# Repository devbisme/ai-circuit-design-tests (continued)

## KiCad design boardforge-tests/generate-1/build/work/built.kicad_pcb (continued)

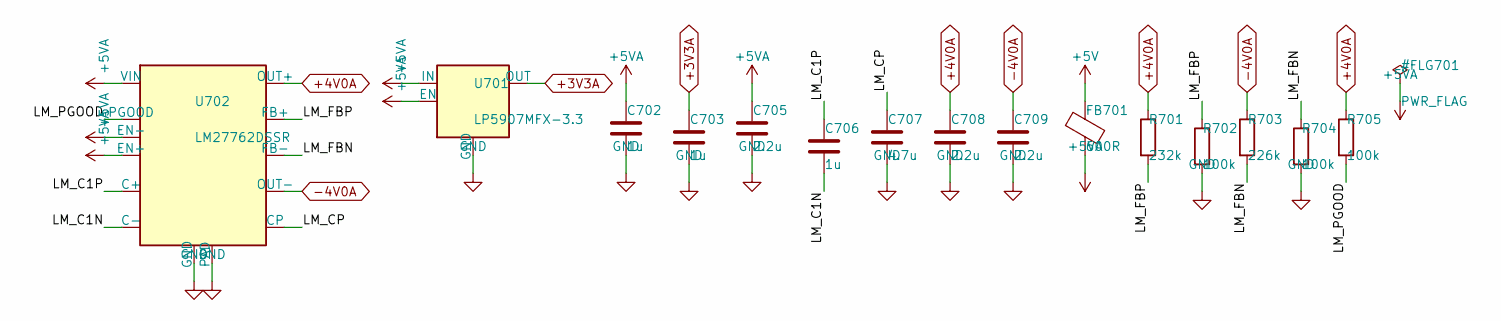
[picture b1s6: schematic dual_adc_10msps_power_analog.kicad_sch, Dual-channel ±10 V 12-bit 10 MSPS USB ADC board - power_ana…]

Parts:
C702, C703, C706: 1u; C_0402_1005Metric; MPN CL05A105KA5NQNC; LCSC C52923
C705, C708, C709: 2.2u; C_0603_1608Metric; MPN CL10A225KO8NNNC; LCSC C23630
C707: 4.7u; C_0603_1608Metric; MPN CL10A475KO8NNNC; LCSC C19666
FB701: 600R; L_0603_1608Metric; MPN BLM18KG601SN1D; LCSC C85833
R701: 232k; R_0402_1005Metric; MPN FRC0402F2323TS; LCSC C3013159
R702, R704, R705: 100k; R_0402_1005Metric; MPN 0402WGF1003TCE; LCSC C25741
R703: 226k; R_0402_1005Metric; MPN FRC0402F2263TS; LCSC C5121518
U701: LP5907MFX-3.3; SOT-23-5; MPN LP5907MFX-3.3/NOPB; LCSC C80670
U702: LM27762DSSR; WSON-12-1EP_3x2mm_P0.5mm_EP1x2.65; MPN LM27762DSSR; LCSC C473398

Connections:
+3V3A: C703.1, U701.5 (OUT); also elsewhere on the board
+4V0A: C708.1, R701.1, R705.1, U702.11 (OUT+); also elsewhere on the board
+5V: FB701.1; also elsewhere on the board
+5VA: C702.1, C705.1, FB701.2, U701.1 (IN), U701.3 (EN), U702.3 (VIN), U702.8 (EN-), U702.12 (EN+)
-4V0A: C709.1, R703.1, U702.6 (OUT-); also elsewhere on the board
/power_analog/LM_C1N: C706.2, U702.9 (C-)
/power_analog/LM_C1P: C706.1, U702.10 (C+)
/power_analog/LM_CP: C707.1, U702.5 (CP)
/power_analog/LM_FBN: R703.2, R704.1, U702.7 (FB-)
/power_analog/LM_FBP: R701.2, R702.1, U702.2 (FB+)
/power_analog/LM_PGOOD: R705.2, U702.1 (PGOOD)
GND: C702.2, C703.2, C705.2, C707.2, C708.2, C709.2, R702.2, R704.2, U701.2 (GND), U702.4 (GND), U702.13 (PAD); also elsewhere on the board

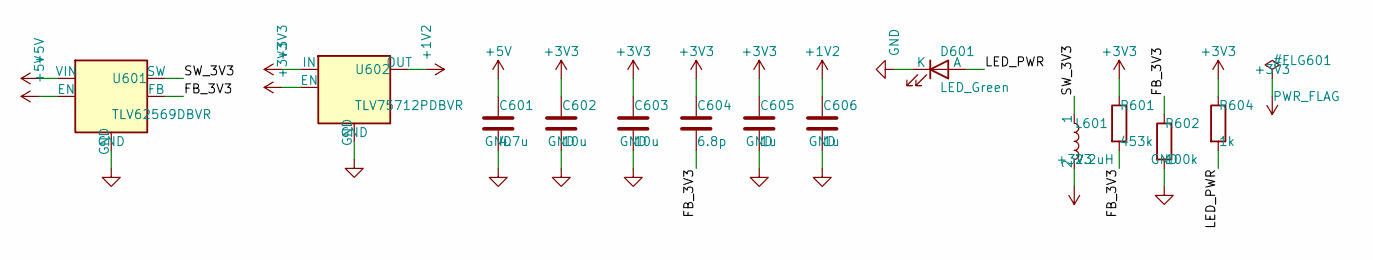
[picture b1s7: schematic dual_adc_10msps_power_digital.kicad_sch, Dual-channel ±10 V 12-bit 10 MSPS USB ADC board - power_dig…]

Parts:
C601: 4.7u; C_0603_1608Metric; MPN CL10A475KO8NNNC; LCSC C19666
C602, C603: 10u; C_0603_1608Metric; MPN CL10A106KP8NNNC; LCSC C19702
C604: 6.8p; C_0402_1005Metric; MPN 0402CG6R8C500NT; LCSC C1576
C605, C606: 1u; C_0402_1005Metric; MPN CL05A105KA5NQNC; LCSC C52923
D601: LED_Green; LED_0603_1608Metric; MPN PSC-1608U52GC-G4; LCSC C22371297
L601: 2.2uH; L_1008_2520Metric; MPN TMS252012ALM-2R2MTAA; LCSC C1017131
R601: 453k; R_0402_1005Metric; MPN 0402WGF4533TCE; LCSC C27009
R602: 100k; R_0402_1005Metric; MPN 0402WGF1003TCE; LCSC C25741
R604: 1k; R_0402_1005Metric; MPN 0402WGF1001TCE; LCSC C11702
U601: TLV62569DBVR; SOT-23-5; MPN TLV62569DBVR; LCSC C141836
U602: TLV75712PDBVR; SOT-23-5; MPN TLV75712PDBVR; LCSC C1509296

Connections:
+1V2: C606.1, U602.5 (OUT); also elsewhere on the board
+3V3: C602.1, C603.1, C604.1, C605.1, L601.2, R601.1, R604.1, U602.1 (IN), U602.3 (EN); also elsewhere on the board
+5V: C601.1, U601.1 (EN), U601.4 (VIN); also elsewhere on the board
/power_digital/FB_3V3: C604.2, R601.2, R602.1, U601.5 (FB)
/power_digital/LED_PWR: D601.2 (A), R604.2
/power_digital/SW_3V3: L601.1, U601.3 (SW)
GND: C601.2, C602.2, C603.2, C605.2, C606.2, D601.1 (K), R602.2, U601.2 (GND), U602.2 (GND); also elsewhere on the board

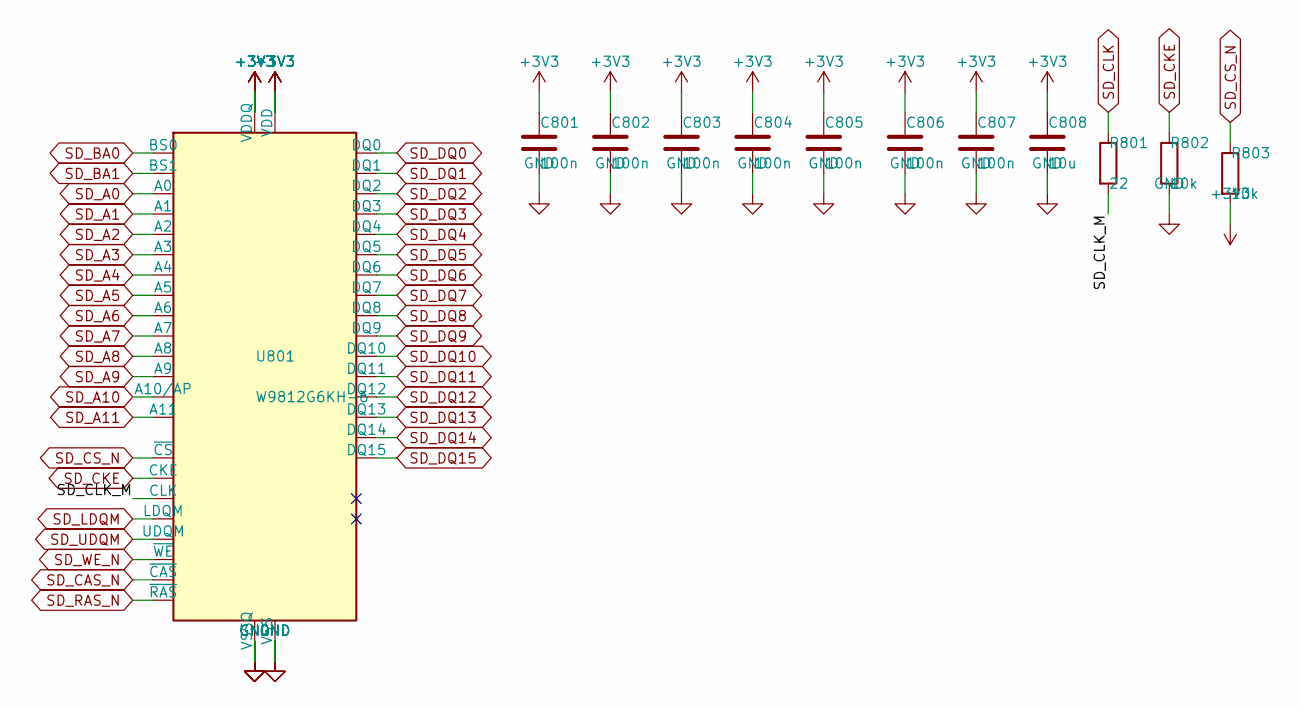
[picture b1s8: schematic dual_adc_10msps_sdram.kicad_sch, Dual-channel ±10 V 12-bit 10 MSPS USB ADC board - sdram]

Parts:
C801, C802, C803, C804, C805, C806, C807: 100n; C_0402_1005Metric; MPN CL05B104KB54PNC; LCSC C307331
C808: 10u; C_0603_1608Metric; MPN CL10A106KP8NNNC; LCSC C19702
R801: 22; R_0402_1005Metric; MPN 0402WGF220JTCE; LCSC C25092
R802, R803: 10k; R_0402_1005Metric; MPN 0402WGF1002TCE; LCSC C25744
U801: W9812G6KH-6; TSOP-II-54_22.2x10.16mm_P0.8mm; MPN W9812G6KH-6; LCSC C62379

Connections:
+3V3: C801.1, C802.1, C803.1, C804.1, C805.1, C806.1, C807.1, C808.1, R803.2, U801.1 (VDD), U801.3 (VDDQ), U801.9 (VDDQ), U801.14 (VDD), U801.27 (VDD), U801.43 (VDDQ), U801.49 (VDDQ); also elsewhere on the board
/sdram/SD_CLK_M: R801.2, U801.38 (CLK)
GND: C801.2, C802.2, C803.2, C804.2, C805.2, C806.2, C807.2, C808.2, R802.2, U801.6 (VSSQ), U801.12 (VSSQ), U801.28 (VSS), U801.41 (VSS), U801.46 (VSSQ), U801.52 (VSSQ), U801.54 (VSS); also elsewhere on the board
SD_A0: U801.23 (A0); also elsewhere on the board
SD_A1: U801.24 (A1); also elsewhere on the board
SD_A2: U801.25 (A2); also elsewhere on the board
SD_A3: U801.26 (A3); also elsewhere on the board
SD_A4: U801.29 (A4); also elsewhere on the board
SD_A5: U801.30 (A5); also elsewhere on the board
SD_A6: U801.31 (A6); also elsewhere on the board
SD_A7: U801.32 (A7); also elsewhere on the board
SD_A8: U801.33 (A8); also elsewhere on the board
SD_A9: U801.34 (A9); also elsewhere on the board
SD_A10: U801.22 (A10/AP); also elsewhere on the board
SD_A11: U801.35 (A11); also elsewhere on the board
SD_BA0: U801.20 (BS0); also elsewhere on the board
SD_BA1: U801.21 (BS1); also elsewhere on the board
SD_CAS_N: U801.17 (~CAS); also elsewhere on the board
SD_CKE: R802.1, U801.37 (CKE); also elsewhere on the board
SD_CLK: R801.1; also elsewhere on the board
SD_CS_N: R803.1, U801.19 (~CS); also elsewhere on the board
SD_DQ0: U801.2 (DQ0); also elsewhere on the board
SD_DQ1: U801.4 (DQ1); also elsewhere on the board
SD_DQ2: U801.5 (DQ2); also elsewhere on the board
SD_DQ3: U801.7 (DQ3); also elsewhere on the board
SD_DQ4: U801.8 (DQ4); also elsewhere on the board
SD_DQ5: U801.10 (DQ5); also elsewhere on the board
SD_DQ6: U801.11 (DQ6); also elsewhere on the board
SD_DQ7: U801.13 (DQ7); also elsewhere on the board
SD_DQ8: U801.42 (DQ8); also elsewhere on the board
SD_DQ9: U801.44 (DQ9); also elsewhere on the board
SD_DQ10: U801.45 (DQ10); also elsewhere on the board
SD_DQ11: U801.47 (DQ11); also elsewhere on the board
SD_DQ12: U801.48 (DQ12); also elsewhere on the board
SD_DQ13: U801.50 (DQ13); also elsewhere on the board
SD_DQ14: U801.51 (DQ14); also elsewhere on the board
SD_DQ15: U801.53 (DQ15); also elsewhere on the board
SD_LDQM: U801.15 (LDQM); also elsewhere on the board
SD_RAS_N: U801.18 (~RAS); also elsewhere on the board
SD_UDQM: U801.39 (UDQM); also elsewhere on the board
SD_WE_N: U801.16 (~WE); also elsewhere on the board

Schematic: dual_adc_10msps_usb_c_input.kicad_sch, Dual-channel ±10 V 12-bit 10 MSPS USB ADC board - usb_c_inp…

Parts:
C501: 1u; C_0402_1005Metric; MPN CL05A105KA5NQNC; LCSC C52923
D501: SMF5.0A; D_SOD-123F; MPN SMF5.0A; LCSC C19077497
F501: 750mA; Fuse_1812_4532Metric; MPN JK-mSMD075-33; LCSC C369169
J501: TYPE-C-31-M-12; USB_C_Receptacle_HRO_TYPE-C-31-M-12; MPN TYPE-C-31-M-12; LCSC C165948
R501, R502: 5.1k; R_0402_1005Metric; MPN 0402WGF5101TCE; LCSC C25905
U501: USBLC6-2SC6; SOT-23-6; MPN USBLC6-2SC6; LCSC C7519

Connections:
+5V: F501.2; also elsewhere on the board
/usb_c_input/CC1: J501.A5 (CC1), R501.1
/usb_c_input/CC2: J501.B5 (CC2), R502.1
GND: C501.2, D501.2 (A2), J501.A1 (GND), J501.A12 (GND), J501.B1 (GND), J501.B12 (GND), J501.SH (SHIELD), R501.2, R502.2, U501.2 (GND); also elsewhere on the board
USB_DM: J501.A7 (D-), J501.B7 (D-), U501.3 (I/O2), U501.4 (I/O2); also elsewhere on the board
USB_DP: J501.A6 (D+), J501.B6 (D+), U501.1 (I/O1), U501.6 (I/O1); also elsewhere on the board
VBUS: C501.1, D501.1 (A1), F501.1, J501.A4 (VBUS), J501.A9 (VBUS), J501.B4 (VBUS), J501.B9 (VBUS), U501.5 (VBUS)

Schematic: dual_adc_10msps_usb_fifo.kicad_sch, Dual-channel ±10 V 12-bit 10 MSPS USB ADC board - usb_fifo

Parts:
C901, C902: 18p; C_0402_1005Metric; MPN 0402CG180J500NT; LCSC C1549
C903, C909: 4.7u; C_0603_1608Metric; MPN CL10A475KO8NNNC; LCSC C19666
C904, C905, C906, C907, C908, C910, C911, C912, C913: 100n; C_0402_1005Metric; MPN CL05B104KB54PNC; LCSC C307331
FB901: 600R; L_0603_1608Metric; MPN BLM18KG601SN1D; LCSC C85833
R901: 12k; R_0402_1005Metric; MPN 0402WGF1202TCE; LCSC C25752
R902, R904, R905, R906, R907, R908, R909, R911, R912: 10k; R_0402_1005Metric; MPN 0402WGF1002TCE; LCSC C25744
R903: 2.2k; R_0402_1005Metric; MPN 0402WGF2201TCE; LCSC C25879
R910: 22; R_0402_1005Metric; MPN 0402WGF220JTCE; LCSC C25092
U901: FT232HL; LQFP-48_7x7mm_P0.5mm; MPN FT232HL; LCSC C51997
U902: 93LC56BT-I/OT; SOT-23-6; MPN 93LC56BT-I/OT; LCSC C190271
Y901: 12MHz; Crystal_SMD_2520-4Pin_2.5x2.0mm; MPN TXM12M0004252FBCEO00T; LCSC C284155

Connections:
+3V3: C906.1, C907.1, C908.1, C909.1, C910.1, C913.1, FB901.1, R902.2, R904.2, R905.2, R906.2, R907.2, R908.2, R909.2, R911.2, R912.2, U901.12 (VCCIO), U901.24 (VCCIO), U901.39 (VCCD), U901.40 (VREGIN), U901.46 (VCCIO), U902.6 (VCC); also elsewhere on the board
/usb_fifo/+3V3_PHY: C903.1, C904.1, C905.1, FB901.2, U901.3 (VPHY), U901.8 (VPLL)
/usb_fifo/EE_CLK: R905.1, U901.44 (EECLK), U902.4 (CLK)
/usb_fifo/EE_CS: R904.1, U901.45 (EECS), U902.5 (CS)
/usb_fifo/EE_DATA: R903.2, R906.1, U901.43 (EEDATA), U902.3 (DI)
/usb_fifo/EE_DO: R903.1, U902.1 (DO)
/usb_fifo/FT_CLKOUT_S: R910.1, U901.29 (ACBUS5)
/usb_fifo/FT_PWRSAV_N: R912.1, U901.31 (ACBUS7)
/usb_fifo/FT_REF: R901.1, U901.5 (REF)
/usb_fifo/FT_RESET_N: R902.1, U901.34 (~RESET)
/usb_fifo/FT_SIWU_N: R909.1, U901.28 (ACBUS4)
/usb_fifo/FT_VCCA: C912.1, U901.37 (VCCA)
/usb_fifo/FT_VCORE: C911.1, U901.38 (VCCCORE)
/usb_fifo/FT_XI: C901.1, U901.1 (XCSI), Y901.1
/usb_fifo/FT_XO: C902.1, U901.2 (XCSO), Y901.3
FT_CLKOUT: R910.2; also elsewhere on the board
FT_D0: U901.13 (ADBUS0); also elsewhere on the board
FT_D1: U901.14 (ADBUS1); also elsewhere on the board
FT_D2: U901.15 (ADBUS2); also elsewhere on the board
FT_D3: U901.16 (ADBUS3); also elsewhere on the board
FT_D4: U901.17 (ADBUS4); also elsewhere on the board
FT_D5: U901.18 (ADBUS5); also elsewhere on the board
FT_D6: U901.19 (ADBUS6); also elsewhere on the board
FT_D7: U901.20 (ADBUS7); also elsewhere on the board
FT_OE_N: R911.1, U901.30 (ACBUS6); also elsewhere on the board
FT_RD_N: R907.1, U901.26 (ACBUS2); also elsewhere on the board
FT_RXF_N: U901.21 (ACBUS0); also elsewhere on the board
FT_TXE_N: U901.25 (ACBUS1); also elsewhere on the board
FT_WR_N: R908.1, U901.27 (ACBUS3); also elsewhere on the board
GND: C901.2, C902.2, C903.2, C904.2, C905.2, C906.2, C907.2, C908.2, C909.2, C910.2, C911.2, C912.2, C913.2, R901.2, U901.4 (AGND), U901.9 (AGND), U901.10 (GND), U901.11 (GND), U901.22 (GND), U901.23 (GND), U901.35 (GND), U901.36 (GND), U901.41 (AGND), U901.42 (TEST), U901.47 (GND), U901.48 (GND), U902.2 (GND), Y901.2 (G), Y901.4 (G); also elsewhere on the board
USB_DM: U901.6 (DM); also elsewhere on the board
USB_DP: U901.7 (DP); also elsewhere on the board

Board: 4 copper layers, 243 parts (0 on the bottom side), 217 nets, no tracks yet.

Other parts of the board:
H1, H2, H3, H4: MountingHole; MountingHole_3.2mm_M3_Pad_Via

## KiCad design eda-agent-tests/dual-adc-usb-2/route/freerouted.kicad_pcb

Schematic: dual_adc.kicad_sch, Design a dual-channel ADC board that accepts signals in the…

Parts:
C1, C11, C18, C25: 4.7uF
C2, C4, C6, C7, C10, C49, C50, C54, C55: 1uF
C3, C5, C8, C61, C69, C80, C81, C83, C93: 10uF
C9, C12, C13, C48, C51, C53, C56: 2.2uF
C14: 4.7nF
C15, C19, C20, C21, C22, C23, C24, C26, C27, C28, C29, C30, C36, C37, C44, C45, C47, C52, C57, C58, C59, C60, C62, C63, C64, C65, C66, C67, C68, C70, C71, C72, C73, C74, C75, C76, C77, C78, C79, C82, C84, C85, C86, C87, C88, C89, C90, C91, C92: 100nF
C16, C17: 27pF
C31, C39: 12pF
C32, C40: 2.7pF
C33, C41: 22pF
C34, C35, C42, C43: 33pF
C38, C46: 100pF
D1: Green
D2, D3: BAV99
D4, D5: Yellow
F1: 750mA
FB1: 120R@100MHz 2A
FB2, FB3: 600R@100MHz
H1, H2, H3, H4: MountingHole
J1: USB_B
J2: BNC_A
J3: BNC_B
J4: PROG
R1, R9, R10, R12, R13, R14, R33, R40, R41, R42, R43, R44: 10k
R2: 232k
R3, R5: 100k
R4: 226k
R6, R17, R18, R19, R20, R21, R26, R27, R28, R29, R30, R45, R46: 1k
R7: 1M
R8: 12k
R11: 2.2k
R15, R24: 909k
R16, R25: 90.9k
R22, R23, R31, R32: 49.9
R34: 20k
R35, R36, R37: 33
R38, R39: 100
RN1, RN2, RN3, RN4, RN5, RN6, RN7: 33
U1: AP2112K-3.3
U2: AP2112K-1.2
U3: LP5907MFX-3.3
U4: LM27762
U5: USBLC6-2SC6
U6: FT232HL
U7: 93LC56B
U8: OPA1656ID
U9, U10: THS4521ID
U11: LTC2290CUP
U12: ICE40HX4K-TQ144
U13: W25Q32JVSS
U14: MT48LC16M16A2TG-6A
X1: ASE-10.000MHz
Y1: 12MHz

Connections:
+1V2: C5.1, C65.1, C66.1, C67.1, C68.1, C69.1, R38.1, R39.1; also elsewhere on the board
+3V3A: C7.1, C8.1, C36.1, C44.1, C57.1, C58.1, C59.1, C60.1, C61.1, FB3.1, R33.1; also elsewhere on the board
+4V: C12.1, C29.1, D2.2 (A), D3.2 (A), R2.1, U4.11 (OUT+); also elsewhere on the board
+5V: C1.1, C2.1, C6.1, C9.1, FB1.2, U4.3 (VIN), U4.8 (EN-), U4.12 (EN+); also elsewhere on the board
-4V: C13.1, C30.1, D2.1 (K), D3.1 (K), R4.1, U4.6 (OUT-); also elsewhere on the board
ADC_CLKA: R35.2; also elsewhere on the board
ADC_CLKB: R36.2; also elsewhere on the board
ADC_DA0: RN1.8 (R1.2); also elsewhere on the board
ADC_DA0_R: RN1.1 (R1.1); also elsewhere on the board
ADC_DA1: RN1.7 (R2.2); also elsewhere on the board
ADC_DA1_R: RN1.2 (R2.1); also elsewhere on the board
ADC_DA2: RN1.6 (R3.2); also elsewhere on the board
ADC_DA2_R: RN1.3 (R3.1); also elsewhere on the board
ADC_DA3: RN1.5 (R4.2); also elsewhere on the board
ADC_DA3_R: RN1.4 (R4.1); also elsewhere on the board
ADC_DA4: RN2.8 (R1.2); also elsewhere on the board
ADC_DA4_R: RN2.1 (R1.1); also elsewhere on the board
ADC_DA5: RN2.7 (R2.2); also elsewhere on the board
ADC_DA5_R: RN2.2 (R2.1); also elsewhere on the board
ADC_DA6: RN2.6 (R3.2); also elsewhere on the board
ADC_DA6_R: RN2.3 (R3.1); also elsewhere on the board
ADC_DA7: RN2.5 (R4.2); also elsewhere on the board
ADC_DA7_R: RN2.4 (R4.1); also elsewhere on the board
ADC_DA8: RN3.8 (R1.2); also elsewhere on the board
ADC_DA8_R: RN3.1 (R1.1); also elsewhere on the board
ADC_DA9: RN3.7 (R2.2); also elsewhere on the board
ADC_DA9_R: RN3.2 (R2.1); also elsewhere on the board
ADC_DA10: RN3.6 (R3.2); also elsewhere on the board
ADC_DA10_R: RN3.3 (R3.1); also elsewhere on the board
ADC_DA11: RN3.5 (R4.2); also elsewhere on the board
ADC_DA11_R: RN3.4 (R4.1); also elsewhere on the board
ADC_DB0: RN4.7 (R2.2); also elsewhere on the board
ADC_DB0_R: RN4.2 (R2.1); also elsewhere on the board
ADC_DB1: RN4.6 (R3.2); also elsewhere on the board
ADC_DB1_R: RN4.3 (R3.1); also elsewhere on the board
ADC_DB2: RN4.5 (R4.2); also elsewhere on the board
ADC_DB2_R: RN4.4 (R4.1); also elsewhere on the board
ADC_DB3: RN5.8 (R1.2); also elsewhere on the board
ADC_DB3_R: RN5.1 (R1.1); also elsewhere on the board
ADC_DB4: RN5.7 (R2.2); also elsewhere on the board
ADC_DB4_R: RN5.2 (R2.1); also elsewhere on the board
ADC_DB5: RN5.6 (R3.2); also elsewhere on the board
ADC_DB5_R: RN5.3 (R3.1); also elsewhere on the board
ADC_DB6: RN5.5 (R4.2); also elsewhere on the board
ADC_DB6_R: RN5.4 (R4.1); also elsewhere on the board
ADC_DB7: RN6.8 (R1.2); also elsewhere on the board
ADC_DB7_R: RN6.1 (R1.1); also elsewhere on the board
ADC_DB8: RN6.7 (R2.2); also elsewhere on the board
ADC_DB8_R: RN6.2 (R2.1); also elsewhere on the board
ADC_DB9: RN6.6 (R3.2); also elsewhere on the board
ADC_DB9_R: RN6.3 (R3.1); also elsewhere on the board
ADC_DB10: RN6.5 (R4.2); also elsewhere on the board
ADC_DB10_R: RN6.4 (R4.1); also elsewhere on the board
ADC_DB11: RN7.8 (R1.2); also elsewhere on the board
ADC_DB11_R: RN7.1 (R1.1); also elsewhere on the board
ADC_MODE: R33.2, R34.1; also elsewhere on the board
ADC_OFA: RN4.8 (R1.2); also elsewhere on the board
ADC_OFA_R: RN4.1 (R1.1); also elsewhere on the board
ADC_OFB: RN7.7 (R2.2); also elsewhere on the board
ADC_OFB_R: RN7.2 (R2.1); also elsewhere on the board
AINA_N: C38.2, R23.2; also elsewhere on the board
AINA_P: C38.1, R22.2; also elsewhere on the board
AINB_N: C46.2, R32.2; also elsewhere on the board
AINB_P: C46.1, R31.2; also elsewhere on the board
CDONE: J4.8, R40.2; also elsewhere on the board
CFG_SCK: J4.3, U13.6 (CLK); also elsewhere on the board
CFG_SI: J4.7, U13.2 (DO/IO_{1}); also elsewhere on the board
CFG_SO: J4.5, U13.5 (DI/IO_{0}); also elsewhere on the board
CFG_SS_N: J4.1, R42.2, U13.1 (~CS); also elsewhere on the board
CLK10: R35.1, R36.1, R37.1, X1.3 (OUT)
CRESET_N: J4.4, R41.2; also elsewhere on the board
FDAA_ON: C34.1, R19.1, R23.1; also elsewhere on the board
FDAA_OP: C35.1, R21.1, R22.1; also elsewhere on the board
FDAA_SN: C35.2, R20.2, R21.2; also elsewhere on the board
FDAA_SP: C34.2, R18.2, R19.2; also elsewhere on the board
FDAB_ON: C42.1, R28.1, R32.1; also elsewhere on the board
FDAB_OP: C43.1, R30.1, R31.1; also elsewhere on the board
FDAB_SN: C43.2, R29.2, R30.2; also elsewhere on the board
FDAB_SP: C42.2, R27.2, R28.2; also elsewhere on the board
FLASH_HOLD_N: R44.2, U13.7 (~HOLD/~RESET/IO_{3})
FLASH_WP_N: R43.2, U13.3 (~WP/IO_{2})
FPGA_CLK10: R37.2; also elsewhere on the board
FT_ACBUS8: U6.32 (ACBUS8); also elsewhere on the board
FT_ACBUS9: U6.33 (ACBUS9); also elsewhere on the board
FT_CLKOUT: U6.29 (ACBUS5); also elsewhere on the board
FT_D0: U6.13 (ADBUS0); also elsewhere on the board
FT_D1: U6.14 (ADBUS1); also elsewhere on the board
FT_D2: U6.15 (ADBUS2); also elsewhere on the board
FT_D3: U6.16 (ADBUS3); also elsewhere on the board
FT_D4: U6.17 (ADBUS4); also elsewhere on the board
FT_D5: U6.18 (ADBUS5); also elsewhere on the board
FT_D6: U6.19 (ADBUS6); also elsewhere on the board
FT_D7: U6.20 (ADBUS7); also elsewhere on the board
FT_EECLK: R13.2, U6.44 (EECLK); also elsewhere on the board
FT_EECS: R12.2, U6.45 (EECS); also elsewhere on the board
FT_EEDATA: R11.2, R14.2, U6.43 (EEDATA); also elsewhere on the board
FT_EEDO: R11.1; also elsewhere on the board
FT_OE_N: U6.30 (ACBUS6); also elsewhere on the board
FT_PWRSAV_N: R9.2, U6.31 (ACBUS7)
FT_RD_N: U6.26 (ACBUS2); also elsewhere on the board
FT_REF: R8.1, U6.5 (REF)
FT_RESET_N: R10.2, U6.34 (~RESET)
FT_RXF_N: U6.21 (ACBUS0); also elsewhere on the board
FT_SIWU_N: U6.28 (ACBUS4); also elsewhere on the board
FT_TXE_N: U6.25 (ACBUS1); also elsewhere on the board
FT_VCCA: C26.1, U6.37 (VCCA)
FT_VCORE: C27.1, U6.38 (VCCCORE)
FT_VPHY: C18.1, C19.1, C20.1, FB2.2, U6.3 (VPHY), U6.8 (VPLL)
FT_WR_N: U6.27 (ACBUS3); also elsewhere on the board
FT_XI: C16.1, U6.1 (XCSI), Y1.1
FT_XO: C17.1, U6.2 (XCSO), Y1.3
INA_BUF: R18.1; also elsewhere on the board
INA_CLAMP: D2.3 (K), R17.2; also elsewhere on the board
INA_DIV: C32.2, C33.1, R15.2, R16.1, R17.1
INA_RAW: C31.1, C32.1, J2.1 (In), R15.1
INB_BUF: R27.1; also elsewhere on the board
INB_CLAMP: D3.3 (K), R26.2; also elsewhere on the board
INB_DIV: C40.2, C41.1, R24.2, R25.1, R26.1
INB_RAW: C39.1, C40.1, J3.1 (In), R24.1
LED1_A: D4.2 (A), R45.2
LED1_N: D4.1 (K); also elsewhere on the board
LED2_A: D5.2 (A), R46.2
LED2_N: D5.1 (K); also elsewhere on the board
LED_PWR: D1.2 (A), R6.2
LM_CN: C10.2, U4.9 (C-)
LM_CP: C11.1, U4.5 (CP)
LM_CPF: C10.1, U4.10 (C+)
LM_FBN: R4.2, R5.1, U4.7 (FB-)
LM_FBP: R2.2, R3.1, U4.2 (FB+)
LM_PGOOD_N: R1.2, U4.1 (PGOOD); also elsewhere on the board
OSC_VDD: C64.1, FB3.2, X1.1 (EN), X1.4 (Vdd)
REFHA: C47.1, C48.1, C49.1; also elsewhere on the board
REFHB: C52.1, C53.1, C54.1; also elsewhere on the board
REFLA: C47.2, C48.2, C50.1; also elsewhere on the board
REFLB: C52.2, C53.2, C55.1; also elsewhere on the board
SD_A0: U14.23 (A0); also elsewhere on the board
SD_A1: U14.24 (A1); also elsewhere on the board
SD_A2: U14.25 (A2); also elsewhere on the board
SD_A3: U14.26 (A3); also elsewhere on the board
SD_A4: U14.29 (A4); also elsewhere on the board
SD_A5: U14.30 (A5); also elsewhere on the board
SD_A6: U14.31 (A6); also elsewhere on the board
SD_A7: U14.32 (A7); also elsewhere on the board
SD_A8: U14.33 (A8); also elsewhere on the board
SD_A9: U14.34 (A9); also elsewhere on the board
SD_A10: U14.22 (A10); also elsewhere on the board
SD_A11: U14.35 (A11); also elsewhere on the board
SD_A12: U14.36 (A12); also elsewhere on the board
SD_BA0: U14.20 (BA0); also elsewhere on the board
SD_BA1: U14.21 (BA1); also elsewhere on the board
SD_CAS_N: U14.17 (~CAS); also elsewhere on the board
SD_CKE: U14.37 (CKE); also elsewhere on the board
SD_CLK: U14.38 (CLK); also elsewhere on the board
SD_CS_N: U14.19 (~CS); also elsewhere on the board
SD_DQ0: U12.110 (IOT_168), U14.2 (DQ0)
SD_DQ1: U12.112 (IOT_169), U14.4 (DQ1)
SD_DQ2: U12.113 (IOT_170), U14.5 (DQ2)
SD_DQ3: U12.114 (IOT_171), U14.7 (DQ3)
SD_DQ4: U12.115 (IOT_172), U14.8 (DQ4)
SD_DQ5: U12.116 (IOT_173), U14.10 (DQ5)
SD_DQ6: U12.117 (IOT_174), U14.11 (DQ6)
SD_DQ7: U12.118 (IOT_177), U14.13 (DQ7)
SD_DQ8: U12.119 (IOT_178), U14.42 (DQ8)
SD_DQ9: U12.120 (IOT_179), U14.44 (DQ9)
SD_DQ10: U12.121 (IOT_181), U14.45 (DQ10)
SD_DQ11: U12.122 (IOT_190), U14.47 (DQ11)
SD_DQ12: U12.124 (IOT_191), U14.48 (DQ12)
SD_DQ13: U12.125 (IOT_192), U14.50 (DQ13)
SD_DQ14: U12.128 (IOT_197_GBIN1), U14.51 (DQ14)
SD_DQ15: U12.129 (IOT_198_GBIN0), U14.53 (DQ15)
SD_DQMH: U14.39 (DQMH); also elsewhere on the board
SD_DQML: U14.15 (DQML); also elsewhere on the board
SD_RAS_N: U14.18 (~RAS); also elsewhere on the board
SD_WE_N: U14.16 (~WE); also elsewhere on the board
USB_DM: J1.2 (D-), U6.6 (DM); also elsewhere on the board
USB_DP: J1.3 (D+), U6.7 (DP); also elsewhere on the board
USB_SHIELD: C14.1, R7.1; also elsewhere on the board
VBUS: F1.1, J1.1 (VBUS)
VBUS_F: C15.1, F1.2, FB1.1; also elsewhere on the board
VCCPLL0: C81.1, C82.1, R38.2; also elsewhere on the board
VCCPLL1: C83.1, C84.1, R39.2; also elsewhere on the board
VCMA: C37.1, C51.1; also elsewhere on the board
VCMB: C45.1, C56.1; also elsewhere on the board

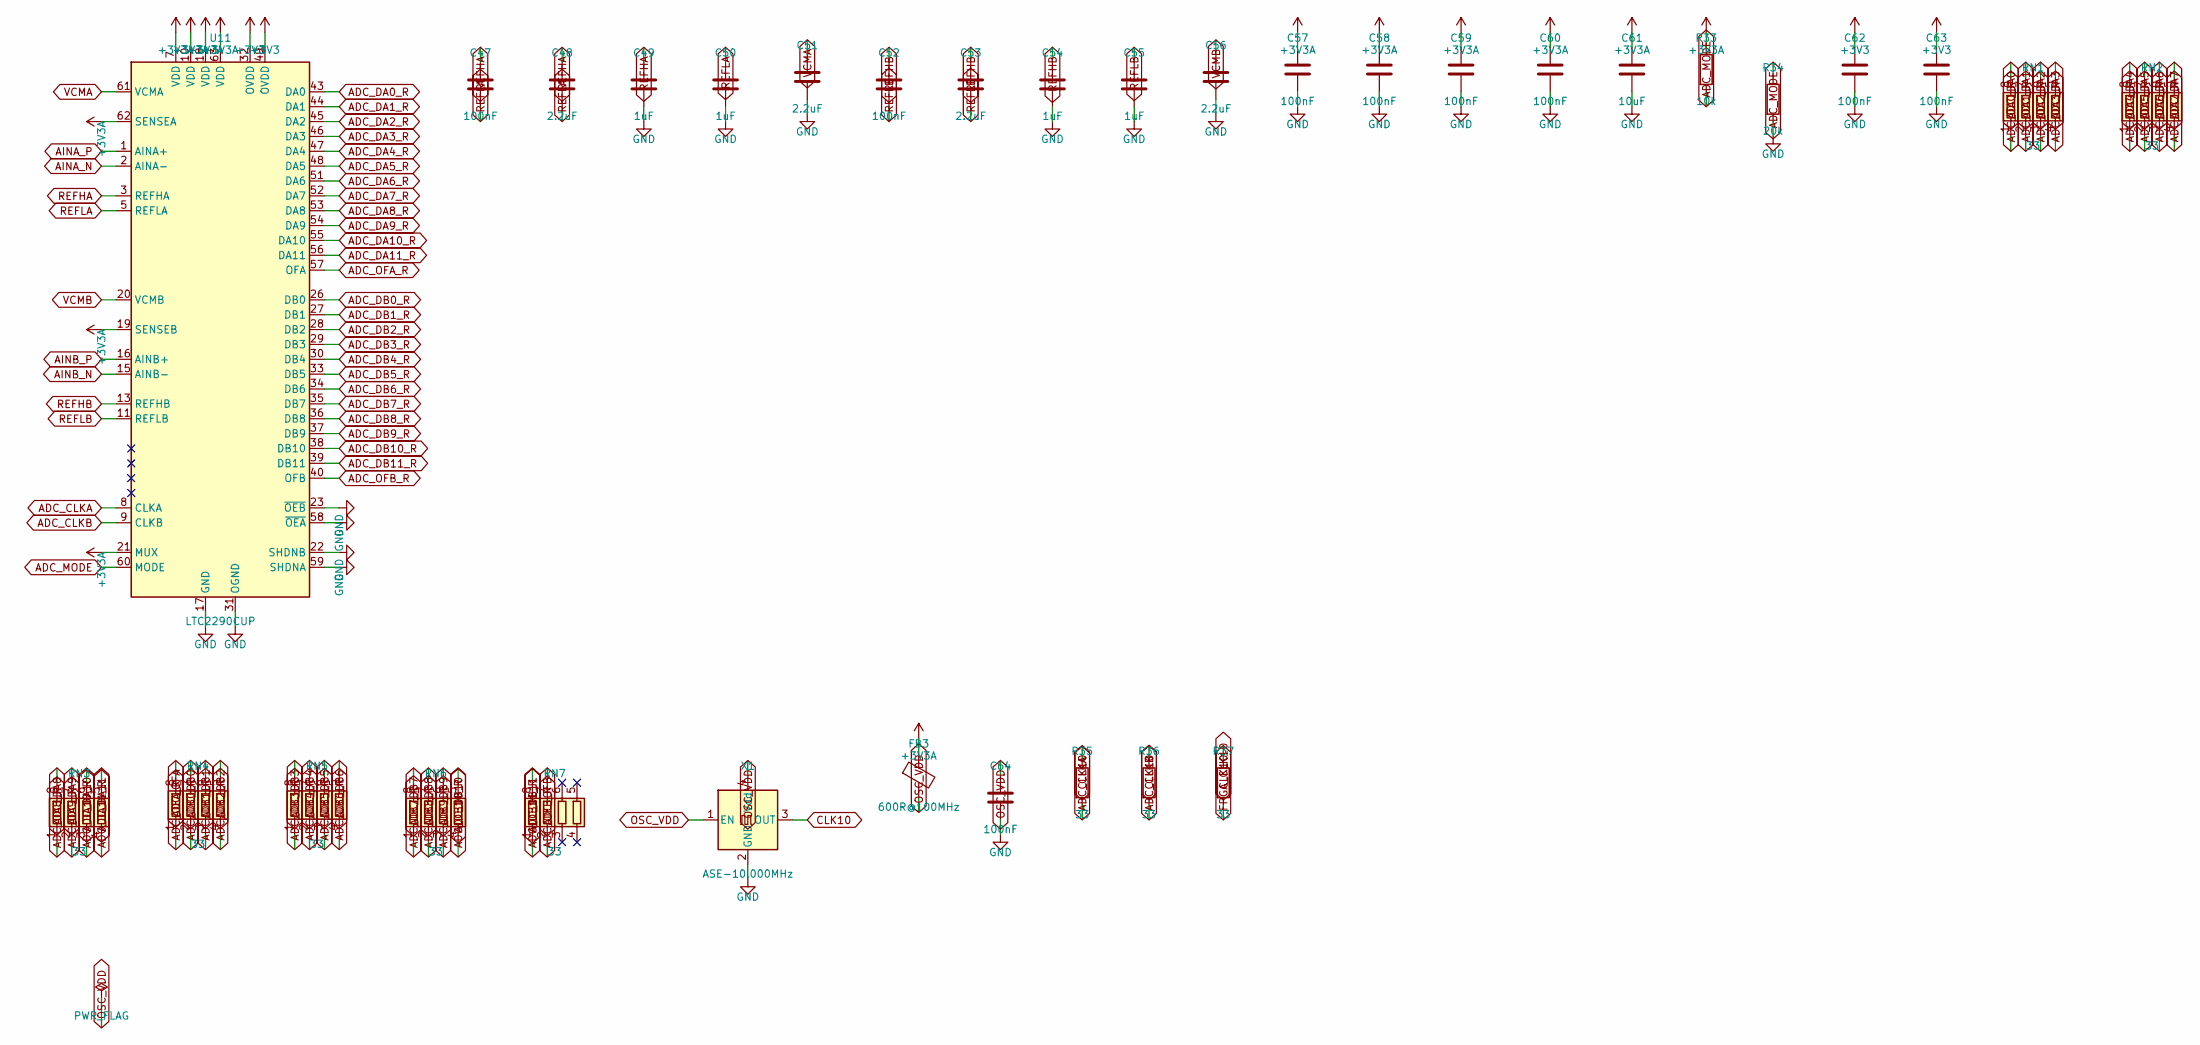
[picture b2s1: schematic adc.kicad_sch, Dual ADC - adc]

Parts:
C47, C52, C57, C58, C59, C60, C62, C63, C64: 100nF; C_0603_1608Metric
C48, C51, C53, C56: 2.2uF; C_0805_2012Metric
C49, C50, C54, C55: 1uF; C_0603_1608Metric
C61: 10uF; C_0805_2012Metric
FB3: 600R@100MHz; L_0603_1608Metric; MPN BLM18AG601SN1D
R33: 10k; R_0603_1608Metric
R34: 20k; R_0603_1608Metric
R35, R36, R37: 33; R_0603_1608Metric
RN1, RN2, RN3, RN4, RN5, RN6, RN7: 33; R_Array_Convex_4x0603; MPN CAY16-330J4LF
U11: LTC2290CUP; QFN-64-1EP_9x9mm_P0.5mm_EP7.15x7.15mm; MPN LTC2290CUP#PBF
X1: ASE-10.000MHz; Oscillator_SMD_Abracon_ASE-4Pin_3.2x2.5mm; MPN ASE-10.000MHZ-LC-T

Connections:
+3V3A: C57.1, C58.1, C59.1, C60.1, C61.1, FB3.1, R33.1, U11.7 (VDD), U11.10 (VDD), U11.18 (VDD), U11.19 (SENSEB), U11.21 (MUX), U11.62 (SENSEA), U11.63 (VDD); also elsewhere on the board
ADC_CLKA: R35.2, U11.8 (CLKA)
ADC_CLKB: R36.2, U11.9 (CLKB)
ADC_DA0: RN1.8 (R1.2); also elsewhere on the board
ADC_DA0_R: RN1.1 (R1.1), U11.43 (DA0)
ADC_DA1: RN1.7 (R2.2); also elsewhere on the board
ADC_DA1_R: RN1.2 (R2.1), U11.44 (DA1)
ADC_DA2: RN1.6 (R3.2); also elsewhere on the board
ADC_DA2_R: RN1.3 (R3.1), U11.45 (DA2)
ADC_DA3: RN1.5 (R4.2); also elsewhere on the board
ADC_DA3_R: RN1.4 (R4.1), U11.46 (DA3)
ADC_DA4: RN2.8 (R1.2); also elsewhere on the board
ADC_DA4_R: RN2.1 (R1.1), U11.47 (DA4)
ADC_DA5: RN2.7 (R2.2); also elsewhere on the board
ADC_DA5_R: RN2.2 (R2.1), U11.48 (DA5)
ADC_DA6: RN2.6 (R3.2); also elsewhere on the board
ADC_DA6_R: RN2.3 (R3.1), U11.51 (DA6)
ADC_DA7: RN2.5 (R4.2); also elsewhere on the board
ADC_DA7_R: RN2.4 (R4.1), U11.52 (DA7)
ADC_DA8: RN3.8 (R1.2); also elsewhere on the board
ADC_DA8_R: RN3.1 (R1.1), U11.53 (DA8)
ADC_DA9: RN3.7 (R2.2); also elsewhere on the board
ADC_DA9_R: RN3.2 (R2.1), U11.54 (DA9)
ADC_DA10: RN3.6 (R3.2); also elsewhere on the board
ADC_DA10_R: RN3.3 (R3.1), U11.55 (DA10)
ADC_DA11: RN3.5 (R4.2); also elsewhere on the board
ADC_DA11_R: RN3.4 (R4.1), U11.56 (DA11)
ADC_DB0: RN4.7 (R2.2); also elsewhere on the board
ADC_DB0_R: RN4.2 (R2.1), U11.26 (DB0)
ADC_DB1: RN4.6 (R3.2); also elsewhere on the board
ADC_DB1_R: RN4.3 (R3.1), U11.27 (DB1)
ADC_DB2: RN4.5 (R4.2); also elsewhere on the board
ADC_DB2_R: RN4.4 (R4.1), U11.28 (DB2)
ADC_DB3: RN5.8 (R1.2); also elsewhere on the board
ADC_DB3_R: RN5.1 (R1.1), U11.29 (DB3)
ADC_DB4: RN5.7 (R2.2); also elsewhere on the board
ADC_DB4_R: RN5.2 (R2.1), U11.30 (DB4)
ADC_DB5: RN5.6 (R3.2); also elsewhere on the board
ADC_DB5_R: RN5.3 (R3.1), U11.33 (DB5)
ADC_DB6: RN5.5 (R4.2); also elsewhere on the board
ADC_DB6_R: RN5.4 (R4.1), U11.34 (DB6)
ADC_DB7: RN6.8 (R1.2); also elsewhere on the board
ADC_DB7_R: RN6.1 (R1.1), U11.35 (DB7)
ADC_DB8: RN6.7 (R2.2); also elsewhere on the board
ADC_DB8_R: RN6.2 (R2.1), U11.36 (DB8)
ADC_DB9: RN6.6 (R3.2); also elsewhere on the board
ADC_DB9_R: RN6.3 (R3.1), U11.37 (DB9)
ADC_DB10: RN6.5 (R4.2); also elsewhere on the board
ADC_DB10_R: RN6.4 (R4.1), U11.38 (DB10)
ADC_DB11: RN7.8 (R1.2); also elsewhere on the board
ADC_DB11_R: RN7.1 (R1.1), U11.39 (DB11)
ADC_MODE: R33.2, R34.1, U11.60 (MODE)
ADC_OFA: RN4.8 (R1.2); also elsewhere on the board
ADC_OFA_R: RN4.1 (R1.1), U11.57 (OFA)
ADC_OFB: RN7.7 (R2.2); also elsewhere on the board
ADC_OFB_R: RN7.2 (R2.1), U11.40 (OFB)
AINA_N: U11.2 (AINA-); also elsewhere on the board
AINA_P: U11.1 (AINA+); also elsewhere on the board
AINB_N: U11.15 (AINB-); also elsewhere on the board
AINB_P: U11.16 (AINB+); also elsewhere on the board
CLK10: R35.1, R36.1, R37.1, X1.3 (OUT)
FPGA_CLK10: R37.2; also elsewhere on the board
OSC_VDD: C64.1, FB3.2, X1.1 (EN), X1.4 (Vdd)
REFHA: C47.1, C48.1, C49.1, U11.3 (REFHA), U11.4 (REFHA)
REFHB: C52.1, C53.1, C54.1, U11.13 (REFHB), U11.14 (REFHB)
REFLA: C47.2, C48.2, C50.1, U11.5 (REFLA), U11.6 (REFLA)
REFLB: C52.2, C53.2, C55.1, U11.11 (REFLB), U11.12 (REFLB)
VCMA: C51.1, U11.61 (VCMA); also elsewhere on the board
VCMB: C56.1, U11.20 (VCMB); also elsewhere on the board
